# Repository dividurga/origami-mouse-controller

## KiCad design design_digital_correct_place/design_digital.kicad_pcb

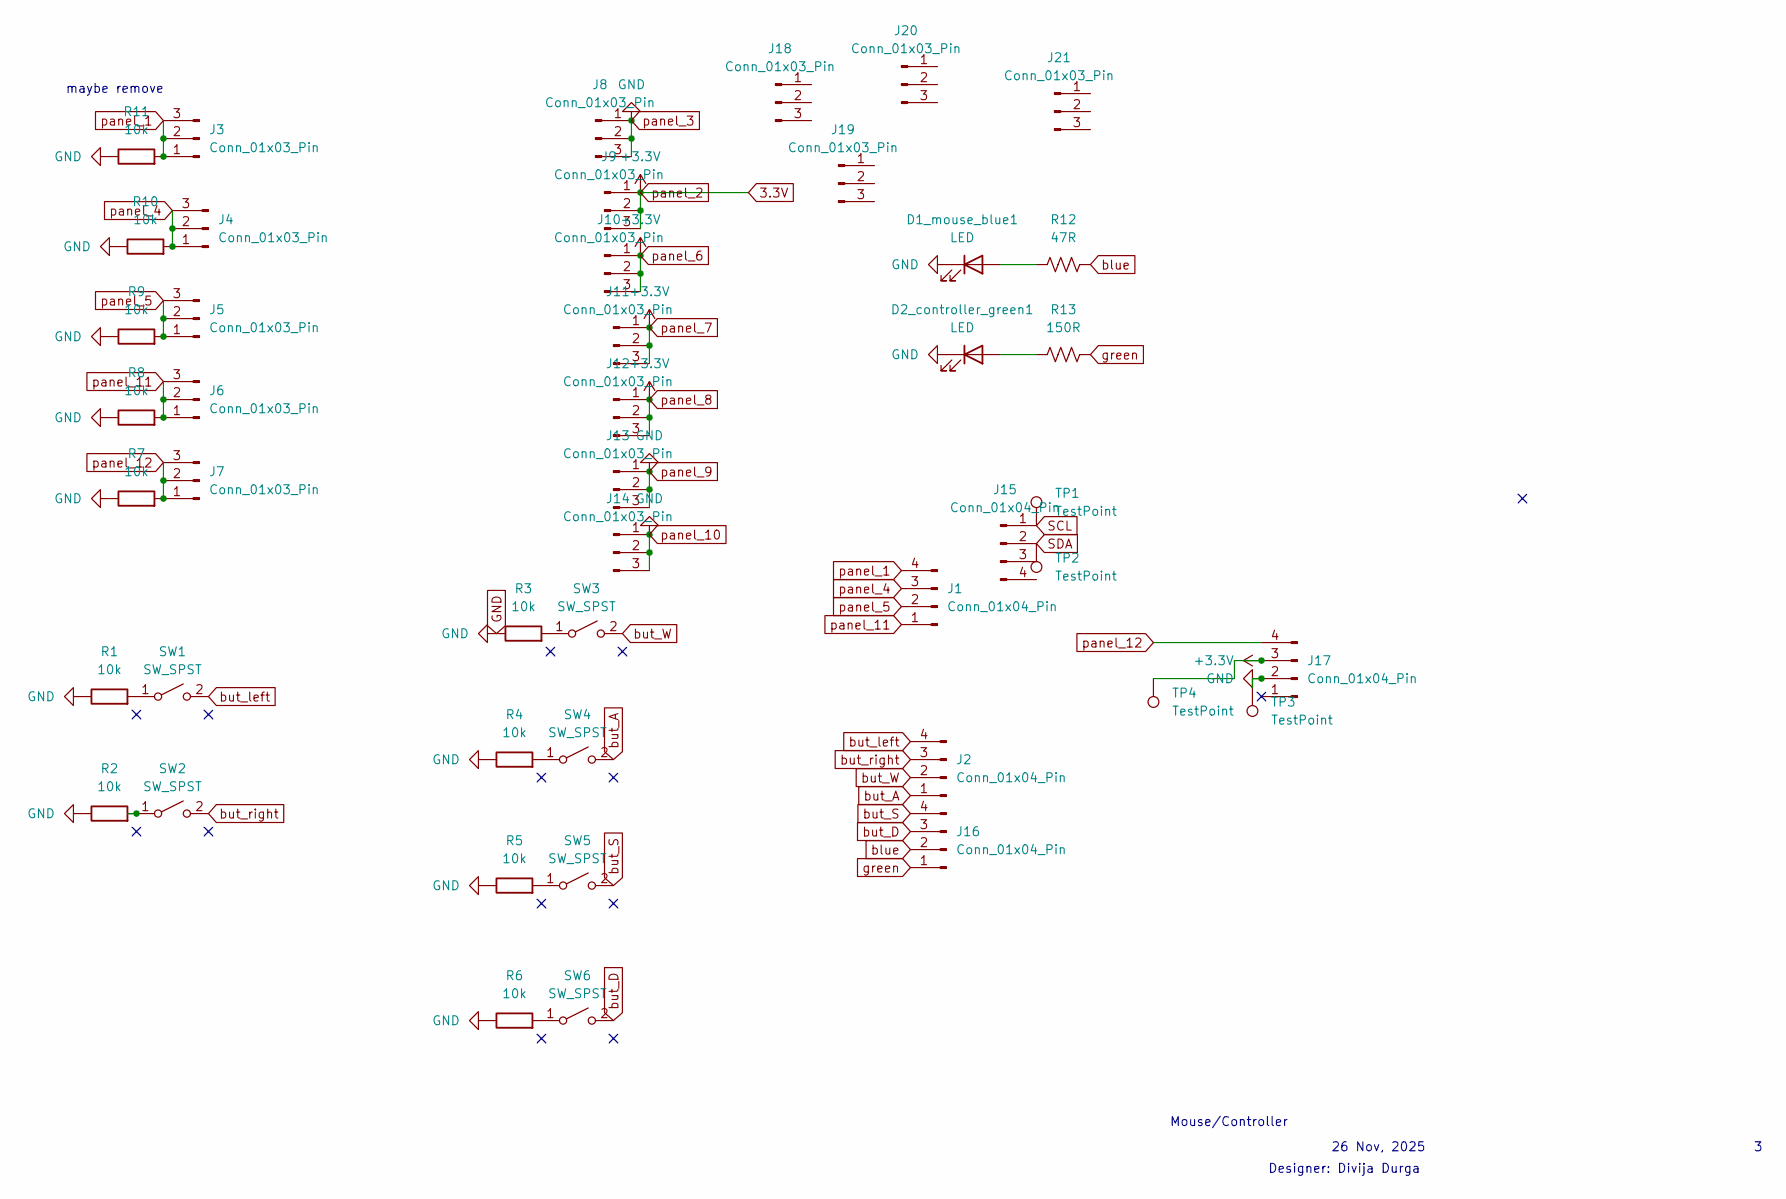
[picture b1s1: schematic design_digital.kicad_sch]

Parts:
D1_mouse_blue1, D2_controller_green1: LED; LED_0603_1608Metric_Pad1.05x0.95mm_HandSolder
J1, J2, J15, J16, J17: Conn_01x04_Pin; JST_SH_BM04B-SRSS-TB_1x04-1MP_P1.00mm_Vertical
J3, J4, J5, J6, J7, J8, J9, J10, J11, J12, J13, J14, J18, J19, J20, J21: Conn_01x03_Pin; PinSocket_1x03_P2.54mm_Horizontal
R1, R2, R3, R4, R5, R6, R7, R8, R9, R10, R11: 10k; R_Axial_DIN0207_L6.3mm_D2.5mm_P7.62mm_Horizontal
R12: 47R; R_Axial_DIN0207_L6.3mm_D2.5mm_P7.62mm_Horizontal
R13: 150R; R_Axial_DIN0207_L6.3mm_D2.5mm_P7.62mm_Horizontal
SW1, SW2: SW_SPST; SW_PUSH-12mm
SW3, SW4, SW5, SW6: SW_SPST; SW_PUSH_6mm
TP1, TP2, TP3, TP4: TestPoint; TestPoint_Pad_D2.0mm

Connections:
3.3V: J9.1, J9.2, J9.3, J10.1, J10.2, J10.3, J11.1, J11.2, J11.3, J12.1, J12.2, J12.3, J17.3, TP4.1
GND: D1_mouse_blue1.1 (K), D2_controller_green1.1 (K), J8.1, J8.2, J8.3, J13.1, J13.2, J13.3, J14.1, J14.2, J14.3, J17.2, R1.1, R2.1, R3.1, R4.1, R5.1, R6.1, R7.1, R8.1, R9.1, R10.1, R11.1, TP3.1
unnamed: D1_mouse_blue1.2 (A), R12.1
unnamed: D2_controller_green1.2 (A), R13.1
unnamed: R1.2, SW1.1 (A)
unnamed: R2.2, SW2.1 (A)
unnamed: R3.2, SW3.1 (A)
unnamed: R4.2, SW4.1 (A)
unnamed: R5.2, SW5.1 (A)
unnamed: R6.2, SW6.1 (A)
SCL: J15.1, TP1.1
SDA: J15.2, TP2.1
blue: J16.2, R12.2
but_A: J2.1, SW4.2 (B)
but_D: J16.3, SW6.2 (B)
but_S: J16.4, SW5.2 (B)
but_W: J2.2, SW3.2 (B)
but_left: J2.4, SW1.2 (B)
but_right: J2.3, SW2.2 (B)
green: J16.1, R13.2
panel_1: J1.4, J3.1, J3.2, J3.3, R11.2
panel_4: J1.3, J4.1, J4.2, J4.3, R10.2
panel_5: J1.2, J5.1, J5.2, J5.3, R9.2
panel_11: J1.1, J6.1, J6.2, J6.3, R8.2
panel_12: J7.1, J7.2, J7.3, J17.4, R7.2

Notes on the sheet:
maybe remove
Mouse/Controller
Designer: Divija Durga
26 Nov, 2025

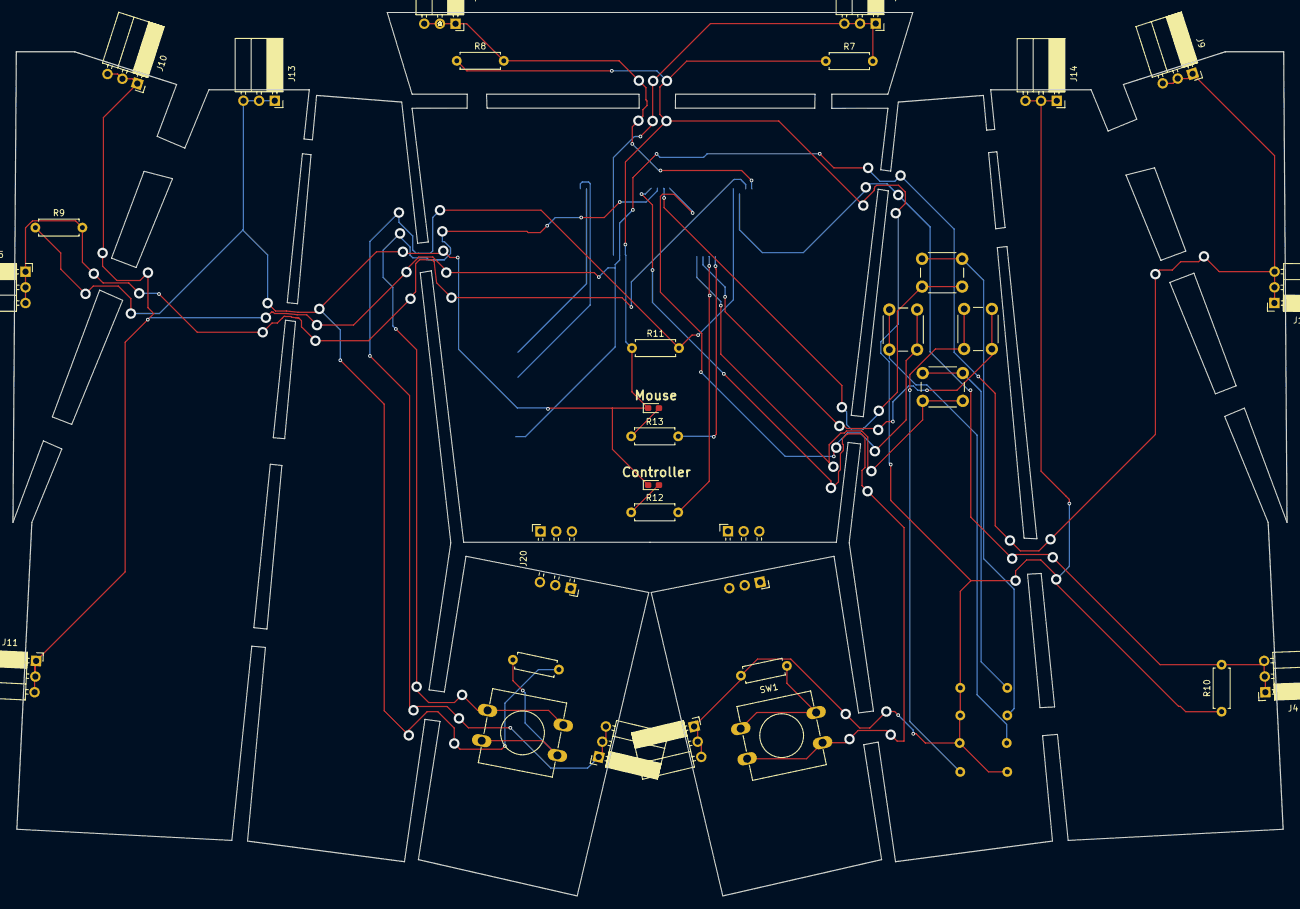
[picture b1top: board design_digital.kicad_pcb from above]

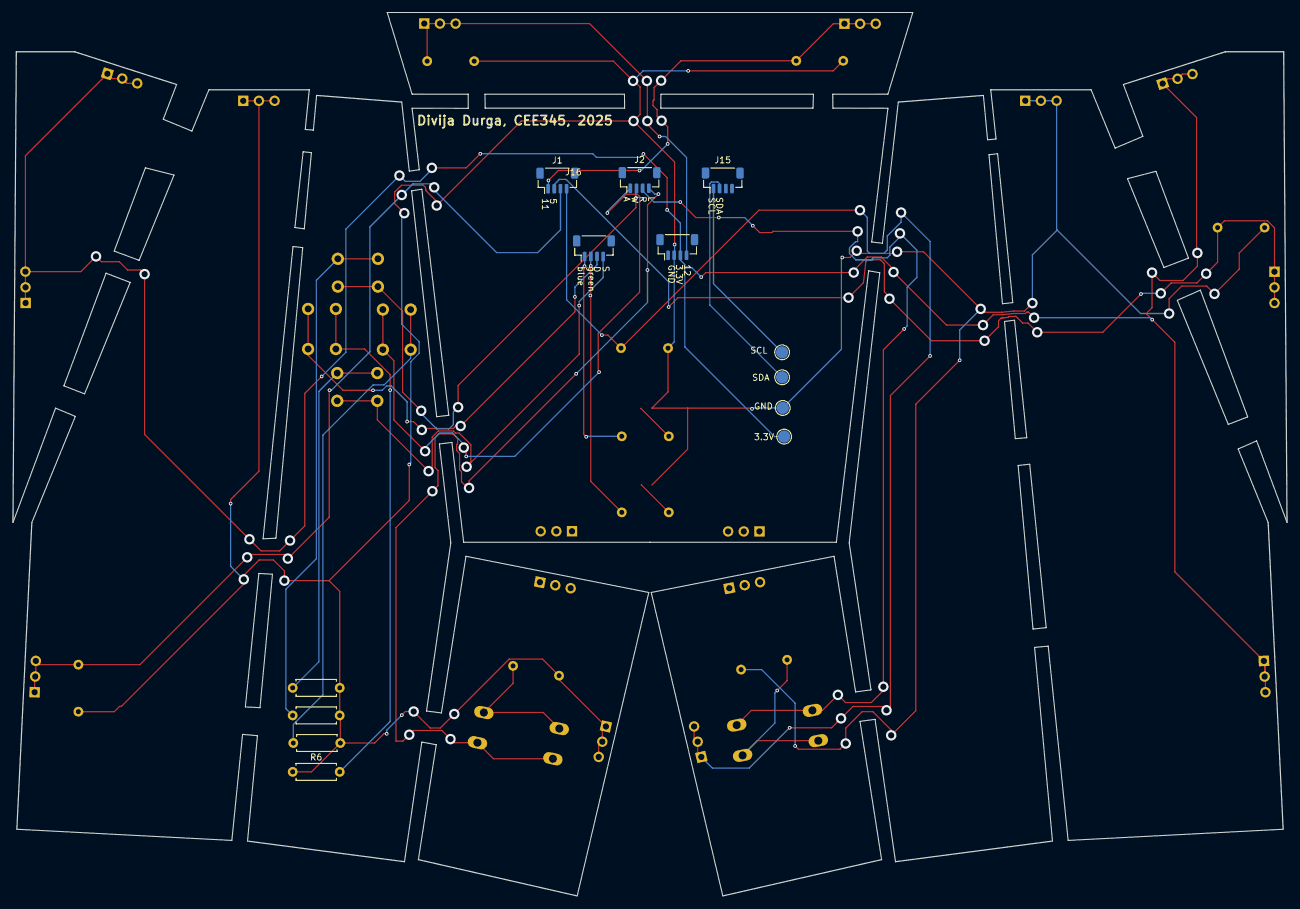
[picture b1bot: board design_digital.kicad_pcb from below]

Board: 2 copper layers, 206.5 x 143.2 mm, 46 parts (13 on the bottom side), 25 nets.

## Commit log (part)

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2025-10-28 Code that detects configuration baseed on simple high/low signal
